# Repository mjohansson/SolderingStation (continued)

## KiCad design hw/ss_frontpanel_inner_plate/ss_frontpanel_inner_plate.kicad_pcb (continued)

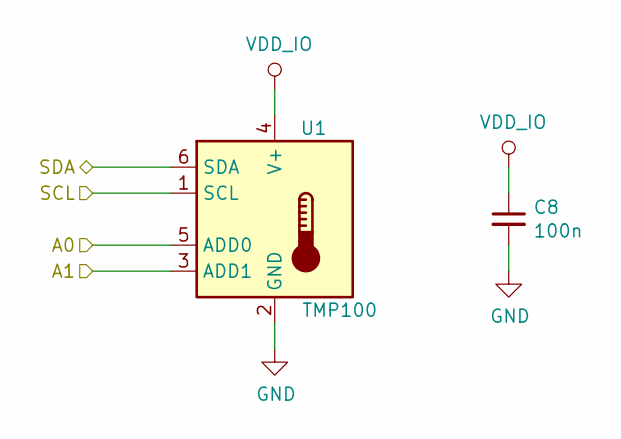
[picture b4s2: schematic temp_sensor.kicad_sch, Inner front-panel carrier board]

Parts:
C8: 100n; C_0603_1608Metric
U1: TMP100; SOT-23-6

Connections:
/SCL: U1.1 (SCL); also elsewhere on the board
/SDA: U1.6 (SDA); also elsewhere on the board
GND: C8.2, U1.2 (GND), U1.3 (ADD1), U1.5 (ADD0); also elsewhere on the board
VDD_IO: C8.1, U1.4 (V+); also elsewhere on the board

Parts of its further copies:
C9, C10, C11, C12: 100n; C_0603_1608Metric
U2, U3, U4, U5: TMP100; SOT-23-6

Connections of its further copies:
/SCL: U2.1 (SCL), U3.1 (SCL), U4.1 (SCL), U5.1 (SCL); also elsewhere on the board
/SDA: U2.6 (SDA), U3.6 (SDA), U4.6 (SDA), U5.6 (SDA); also elsewhere on the board
/TS In mid/A0: U4.5 (ADD0)
GND: C9.2, C10.2, C11.2, C12.2, U2.2 (GND), U2.3 (ADD1), U3.2 (GND), U4.2 (GND), U5.2 (GND), U5.5 (ADD0); also elsewhere on the board
VDD_IO: C9.1, C10.1, C11.1, C12.1, U2.4 (V+), U2.5 (ADD0), U3.3 (ADD1), U3.4 (V+), U3.5 (ADD0), U4.3 (ADD1), U4.4 (V+), U5.3 (ADD1), U5.4 (V+); also elsewhere on the board

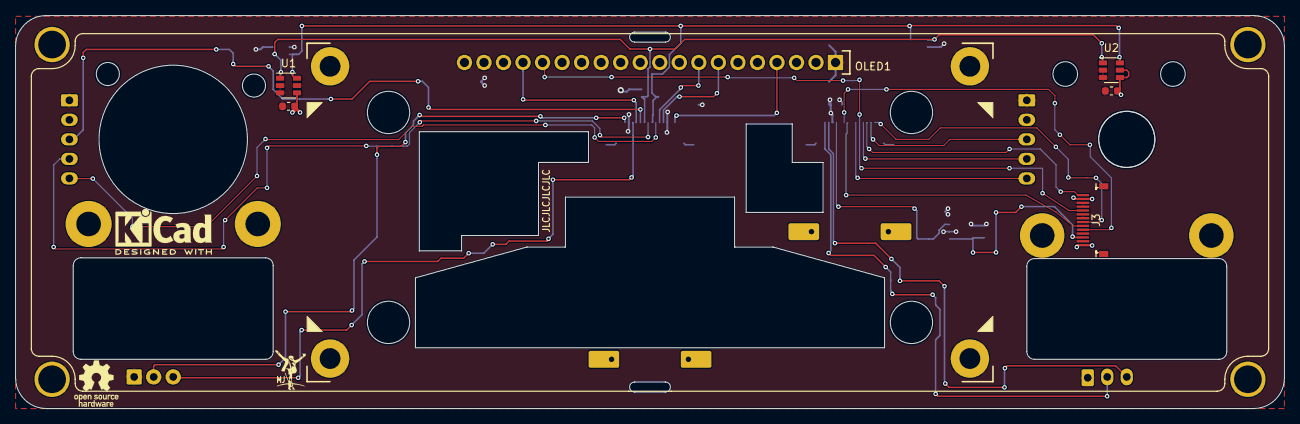
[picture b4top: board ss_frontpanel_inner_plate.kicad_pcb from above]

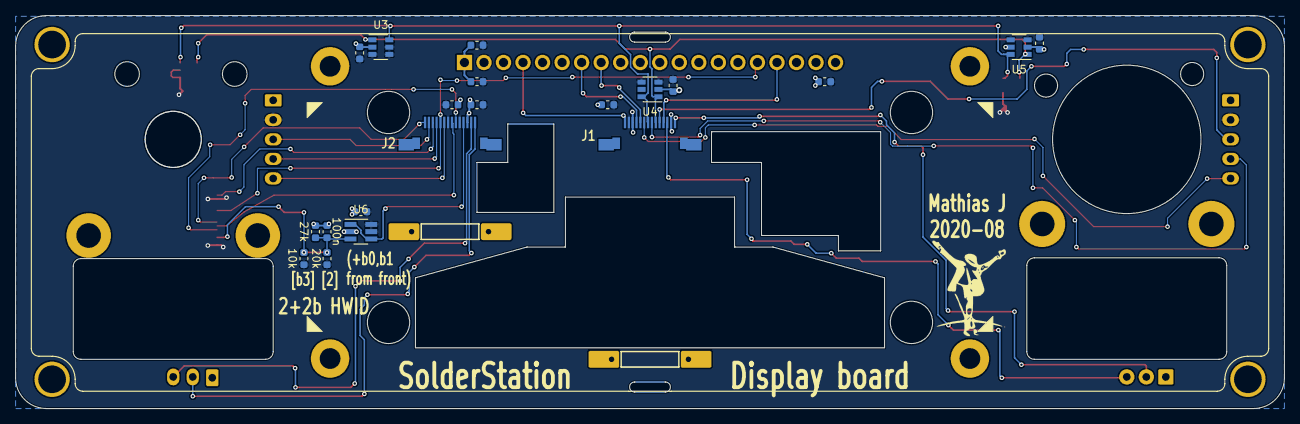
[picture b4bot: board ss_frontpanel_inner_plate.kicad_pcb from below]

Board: 2 copper layers, 165.0 x 51.1 mm, 39 parts (25 on the bottom side), 25 nets.

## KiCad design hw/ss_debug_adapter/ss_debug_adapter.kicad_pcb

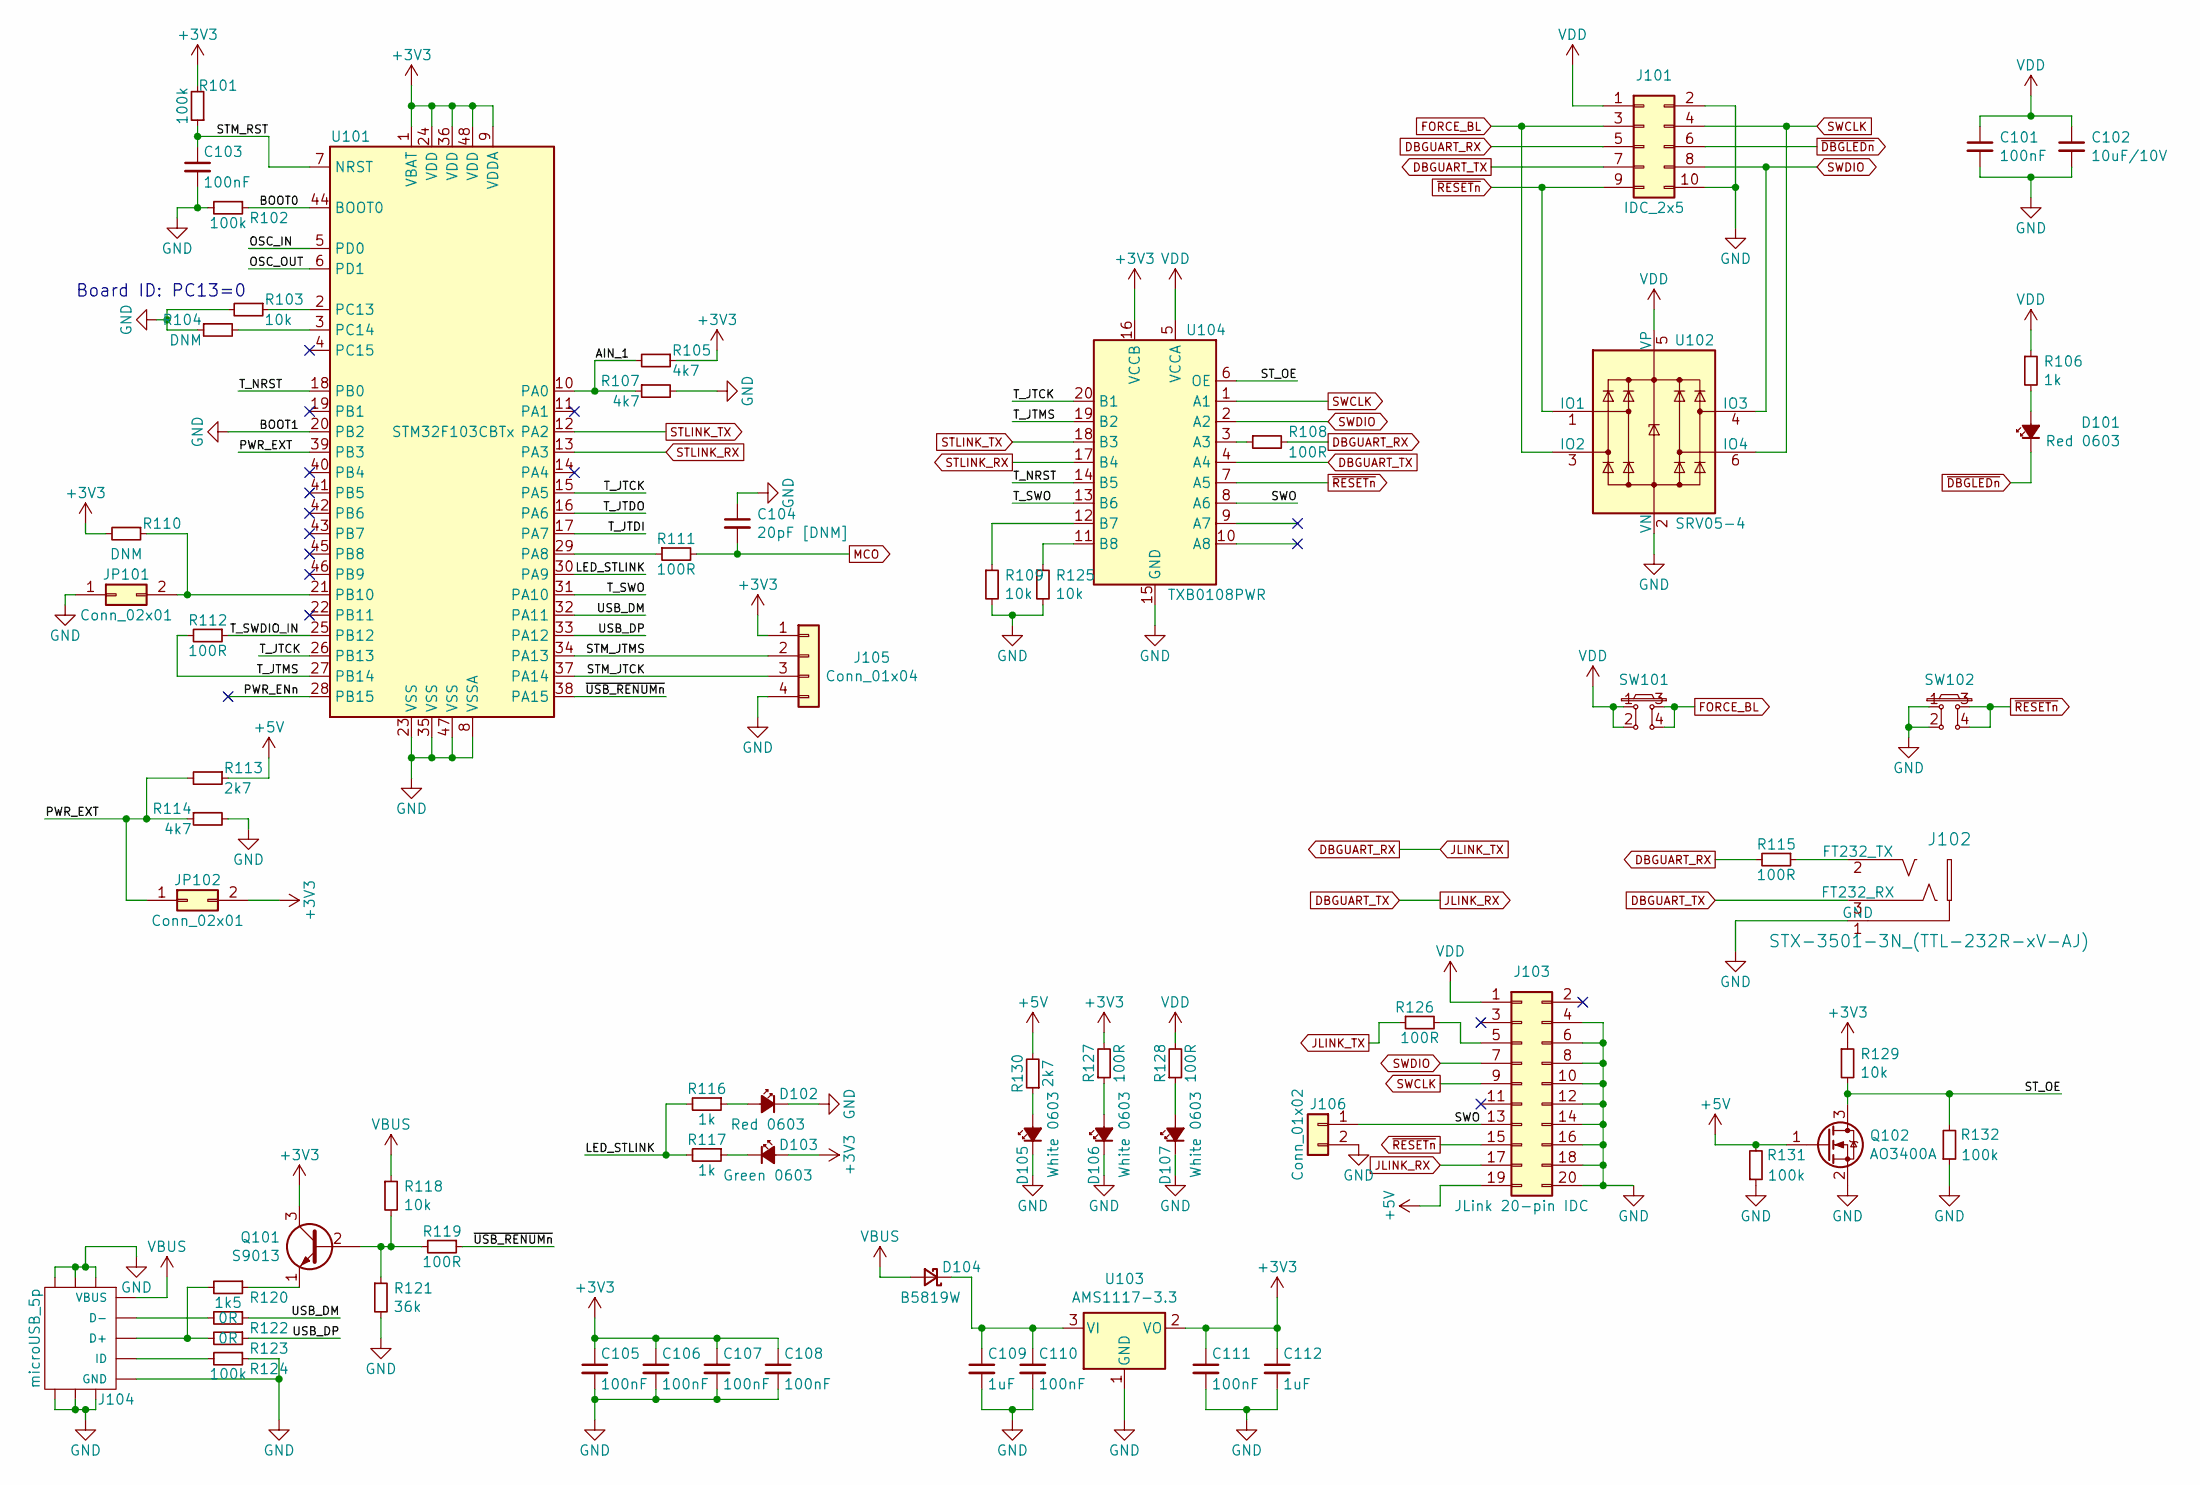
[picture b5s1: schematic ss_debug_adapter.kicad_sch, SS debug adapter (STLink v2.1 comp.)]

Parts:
C101, C103, C105, C106, C107, C108, C110, C111: 100nF; C_0402_1005Metric; LCSC C1525
C102: 10uF/10V; C_0603_1608Metric; LCSC C19702
C104: 20pF [DNM]; C_0402_1005Metric
C109, C112: 1uF; C_0402_1005Metric; LCSC C52923
D101, D102: Red 0603; LED_0603_1608Metric; LCSC C2286
D103: Green 0603; LED_0603_1608Metric; LCSC C72043
D104: B5819W; D_SOD-123; LCSC C6186
D105, D106, D107: White 0603; LED_0603_1608Metric; LCSC C2290
J101: IDC_2x5; IDC-Header_2x05_P2.54mm_Vertical
J102: STX-3501-3N_(TTL-232R-xV-AJ); STX3501_smd
J103: JLink 20-pin IDC; IDC-Header_2x10_P2.54mm_Vertical
J104: microUSB_5p; microUSB_5p-LCSC-Jing_Extension
J105: Conn_01x04; PinHeader_1x04_P2.54mm_Horizontal
J106: Conn_01x02; PinHeader_1x02_P2.54mm_Vertical
JP101, JP102: Conn_02x01; PinHeader_1x02_P2.54mm_Vertical
Q101: S9013; SOT-23; LCSC C6749
Q102: AO3400A; SOT-23
R101, R102, R124, R131, R132: 100k; R_0402_1005Metric; LCSC C25741
R103, R109, R118, R125, R129: 10k; R_0402_1005Metric; LCSC C25744
R104, R110: DNM; R_0402_1005Metric
R105, R107, R114: 4k7; R_0402_1005Metric; LCSC C25900
R106, R116, R117: 1k; R_0402_1005Metric; LCSC C11702
R108, R111, R112, R115, R119, R126, R127, R128: 100R; R_0402_1005Metric; LCSC C25076
R113, R130: 2k7; R_0603_1608Metric; LCSC C13167
R120: 1k5; R_0402_1005Metric; LCSC C25867
R121: 36k; R_0603_1608Metric; LCSC C23147
R122, R123: 0R; R_0402_1005Metric; LCSC C17168
SW101, SW102: Pushbutton_SMD_TS-1102W-4316; SMD_PUSHBTN_6x6mm; LCSC C255812
U101: STM32F103CBTx; LQFP-48_7x7mm_P0.5mm; LCSC C8304
U102: SRV05-4; SOT-23-6; LCSC C85364
U103: AMS1117-3.3; SOT-223-3_TabPin2; LCSC C6186
U104: TXB0108PWR; TSSOP-20_4.4x6.5mm_P0.65mm; JLC Extended

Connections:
+3V3: C105.1, C106.1, C107.1, C108.1, C111.1, C112.1, D103.2 (A), J105.1, JP102.2, Q101.3 (C), R101.2, R105.1, R110.2, R127.2, R129.1, U101.1 (VBAT), U101.9 (VDDA), U101.24 (VDD), U101.36 (VDD), U101.48 (VDD), U103.2 (VO), U104.16 (VCCB)
+5V: J103.19, Q102.1 (G), R113.1, R130.2, R131.2
/AIN_1: R105.2, R107.1, U101.10 (PA0)
/BOOT0: R102.1, U101.44 (BOOT0)
/LED_STLINK: R116.2, R117.2, U101.30 (PA9)
/OSC_IN: U101.5 (PD0)
/OSC_OUT: U101.6 (PD1)
/PWR_ENn: U101.28 (PB15)
/PWR_EXT: JP102.1, R113.2, R114.1, U101.39 (PB3)
/STM_JTCK: J105.3, U101.37 (PA14)
/STM_JTMS: J105.2, U101.34 (PA13)
/STM_RST: C103.1, R101.1, U101.7 (NRST)
/ST_OE: Q102.3 (D), R129.2, R132.2, U104.6 (OE)
/SWO: J103.13, J106.1, U104.8 (A6)
/T_JTCK: U101.15 (PA5), U101.26 (PB13), U104.20 (B1)
/T_JTDI: U101.17 (PA7)
/T_JTDO: U101.16 (PA6)
/T_JTMS: R112.2, U101.27 (PB14), U104.19 (B2)
/T_NRST: U101.18 (PB0), U104.14 (B5)
/T_SWDIO_IN: R112.1, U101.25 (PB12)
/T_SWO: U101.31 (PA10), U104.13 (B6)
/USB_DM: R122.1, U101.32 (PA11)
/USB_DP: R123.1, U101.33 (PA12)
/~USB_RENUMn: R119.1, U101.38 (PA15)
DBGUART_RX: J101.5, R108.2, R115.2, R126.1
DBGUART_TX: J101.7, J102.3 (FT232_RX), J103.17, U104.4 (A4)
FORCE_BL: J101.3, SW101.3, SW101.4, U102.3 (IO2)
GND: C101.2, C102.2, C103.2, C104.1, C105.2, C106.2, C107.2, C108.2, C109.2, C110.2, C111.2, C112.2, D102.1 (K), D105.1 (K), D106.1 (K), D107.1 (K), J101.2, J101.10, J102.1 (GND), J103.4, J103.6, J103.8, J103.10, J103.12, J103.14, J103.16, J103.18, J103.20, J104.5 (GND), J104.6, J104.7, J104.8, J104.9, J104.10, J104.11, J105.4, J106.2, JP101.1, Q102.2 (S), R102.2, R103.2, R104.1, R107.2, R109.2, R114.2, R121.2, R124.1, R125.2, R131.1, R132.1, SW102.1, SW102.2, U101.8 (VSSA), U101.20 (PB2), U101.23 (VSS), U101.35 (VSS), U101.47 (VSS), U102.2 (VN), U103.1 (GND), U104.15 (GND)
MCO: C104.2, R111.2
unnamed: C109.1, C110.1, D104.1 (K), U103.3 (VI)
unnamed: D101.2 (A), R106.2
unnamed: D102.2 (A), R116.1
unnamed: D103.1 (K), R117.1
unnamed: D105.2 (A), R130.1
unnamed: D106.2 (A), R127.1
unnamed: D107.2 (A), R128.1
unnamed: J102.2 (FT232_TX), R115.1
unnamed: J103.5, R126.2
unnamed: J104.2 (D-), R122.2
unnamed: J104.3 (D+), R120.2, R123.2
unnamed: J104.4 (ID), R124.2
unnamed: JP101.2, R110.1, U101.21 (PB10)
unnamed: Q101.1 (E), R120.1
unnamed: Q101.2 (B), R118.2, R119.2, R121.1
unnamed: R103.1, U101.2 (PC13)
unnamed: R104.2, U101.3 (PC14)
unnamed: R108.1, U104.3 (A3)
unnamed: R109.1, U104.12 (B7)
unnamed: R111.1, U101.29 (PA8)
unnamed: R125.1, U104.11 (B8)
STLINK_RX: U101.13 (PA3), U104.17 (B4)
STLINK_TX: U101.12 (PA2), U104.18 (B3)
SWCLK: J101.4, J103.9, U102.6 (IO4), U104.1 (A1)
SWDIO: J101.8, J103.7, U102.4 (IO3), U104.2 (A2)
VBUS: D104.2 (A), J104.1 (VBUS), R118.1
VDD: C101.1, C102.1, J101.1, J103.1, R106.1, R128.2, SW101.1, SW101.2, U102.5 (VP), U104.5 (VCCA)
~DBGLEDn: D101.1 (K), J101.6
~RESETn: J101.9, J103.15, SW102.3, SW102.4, U102.1 (IO1), U104.7 (A5)

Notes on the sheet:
Board ID: PC13=0

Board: 2 copper layers, 67 parts (1 on the bottom side), 53 nets, no tracks yet.

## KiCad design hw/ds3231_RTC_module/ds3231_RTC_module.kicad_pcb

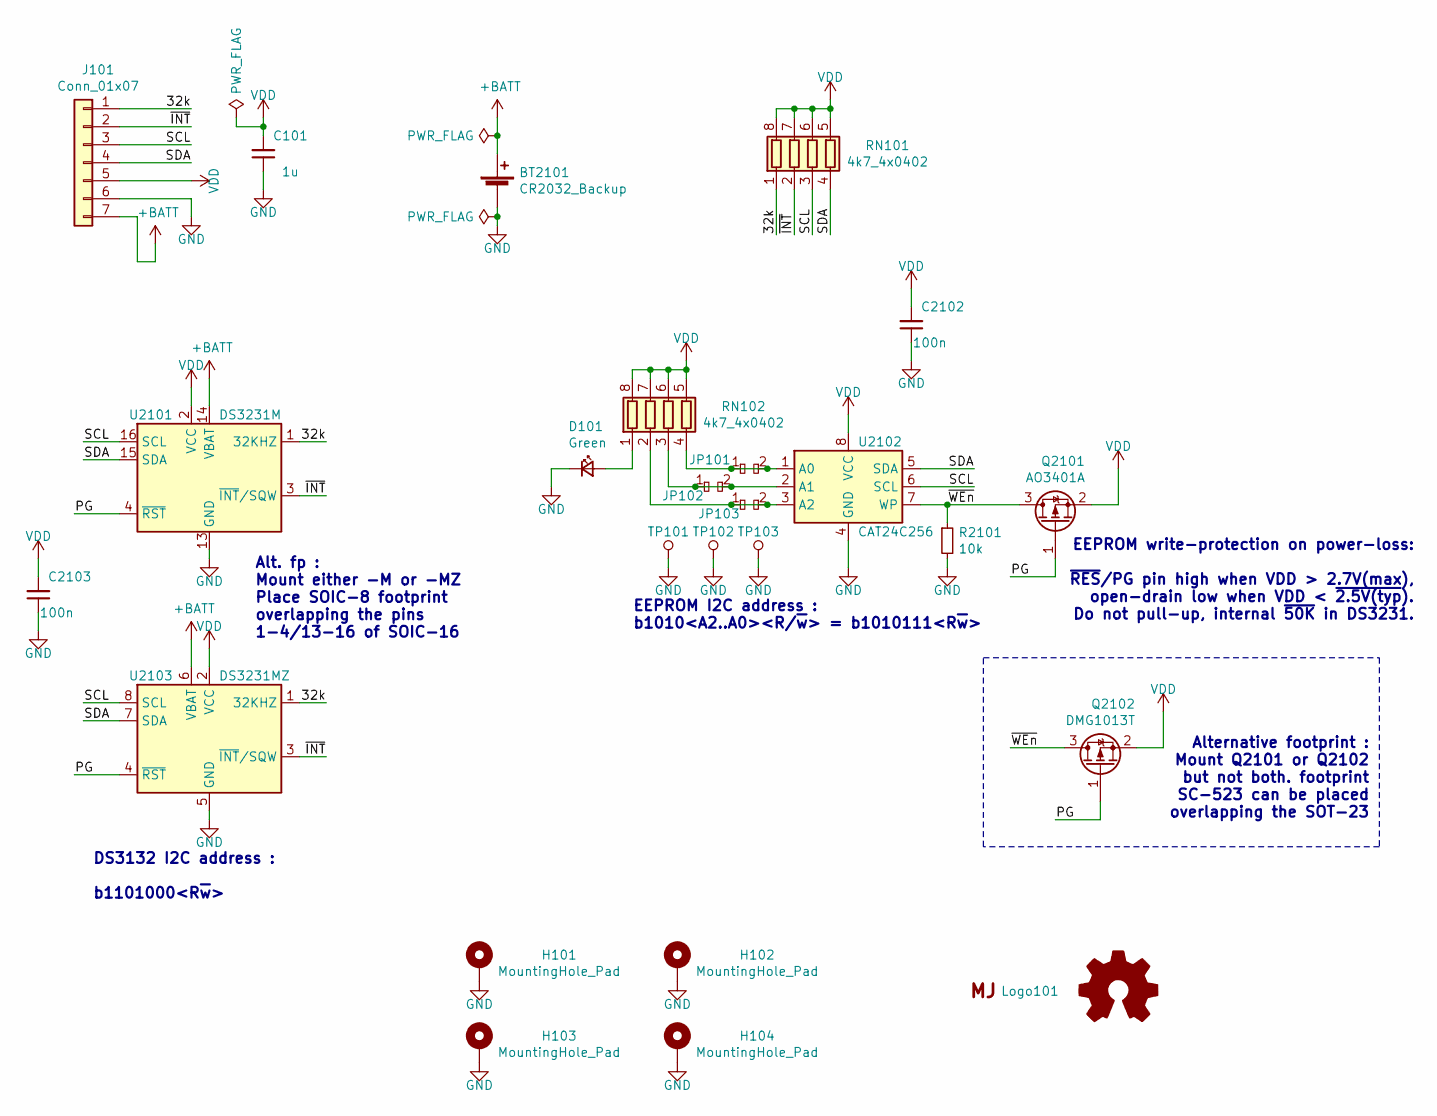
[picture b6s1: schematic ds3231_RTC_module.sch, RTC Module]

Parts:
BT2101: CR2032_Backup; CR2032_coincell_holder
C101: 1u; C_0603_1608Metric
C2102, C2103: 100n; C_0402_1005Metric
D101: Green; LED_0402_1005Metric
H101, H102, H103, H104: MountingHole_Pad; MountingHole_3.2mm_M3_DIN965_Pad
J101: Conn_01x07; PinHeader_1x07_P2.54mm_Vertical
JP101, JP102, JP103: dogbone_2_ud; db2_ud_0402
LOGO101: Logo_Open_Hardware_Small; OSHW-Logo2_7.3x6mm_SilkScreen
Logo101: Logo_MJ; MJ_Mini
Q2101: AO3401A; SOT-23
Q2102: DMG1013T; SOT-523
R2101: 10k; R_0402_1005Metric
RN101, RN102: 4k7_4x0402; R_Array_Convex_4x0402
TP101, TP102, TP103: TP; TP_SMD_1.2c
U2101: DS3231M; SOIC-16W_7.5x10.3mm_P1.27mm
U2102: CAT24C256; SO-8_3.9x4.9mm_P1.27mm
U2103: DS3231MZ; SOIC-8_3.9x4.9mm_P1.27mm

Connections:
+BATT: BT2101.1 (+), J101.7, U2101.14 (VBAT), U2103.6 (VBAT)
/32k: J101.1, RN101.1 (R1.1), U2101.1 (32KHZ), U2103.1 (32KHZ)
/PG: Q2101.1 (G), Q2102.1 (G), U2101.4 (~RST), U2103.4 (~RST)
/SCL: J101.3, RN101.3 (R3.1), U2101.16 (SCL), U2102.6 (SCL), U2103.8 (SCL)
/SDA: J101.4, RN101.4 (R4.1), U2101.15 (SDA), U2102.5 (SDA), U2103.7 (SDA)
/~INT~: J101.2, RN101.2 (R2.1), U2101.3 (~INT~/SQW), U2103.3 (~INT~/SQW)
/~WEn~: Q2101.3 (D), Q2102.3 (D), R2101.1, U2102.7 (WP)
GND: BT2101.2 (-), C101.1, C2102.1, C2103.1, D101.1 (K), H101.1, H102.1, H103.1, H104.1, J101.6, R2101.2, TP101.1, TP102.1, TP103.1, U2101.5 (GND), U2101.6 (GND), U2101.7 (GND), U2101.8 (GND), U2101.9 (GND), U2101.10 (GND), U2101.11 (GND), U2101.12 (GND), U2101.13 (GND), U2102.4 (GND), U2103.5 (GND)
unnamed: D101.2 (A), RN102.1 (R1.1)
unnamed: JP101.1, JP101.2, RN102.4 (R4.1), U2102.1 (A0)
unnamed: JP102.1, JP102.2, RN102.3 (R3.1), U2102.2 (A1)
unnamed: JP103.1, JP103.2, RN102.2 (R2.1), U2102.3 (A2)
VDD: C101.2, C2102.2, C2103.2, J101.5, Q2101.2 (S), Q2102.2 (S), RN101.5 (R4.2), RN101.6 (R3.2), RN101.7 (R2.2), RN101.8 (R1.2), RN102.5 (R4.2), RN102.6 (R3.2), RN102.7 (R2.2), RN102.8 (R1.2), U2101.2 (VCC), U2102.8 (VCC), U2103.2 (VCC)

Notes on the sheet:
Alt. fp : Mount either -M or -MZ Place SOIC-8 footprint overlapping the pins 1-4/13-16 of SOIC-16
EEPROM write-protection on power-loss: ~RES~/PG pin high when VDD > 2.7V(max), open-drain low when VDD < ~2.5V(typ). Do not pull-up, internal ~50K in DS3231.
EEPROM I2C address : b1010<A2..A0><R/~w~> = b1010111<R~w~>
DS3132 I2C address : b1101000<R~w~>
Alternative footprint : Mount Q2101 or Q2102 but not both. footprint SC-523 can be placed overlapping the SOT-23

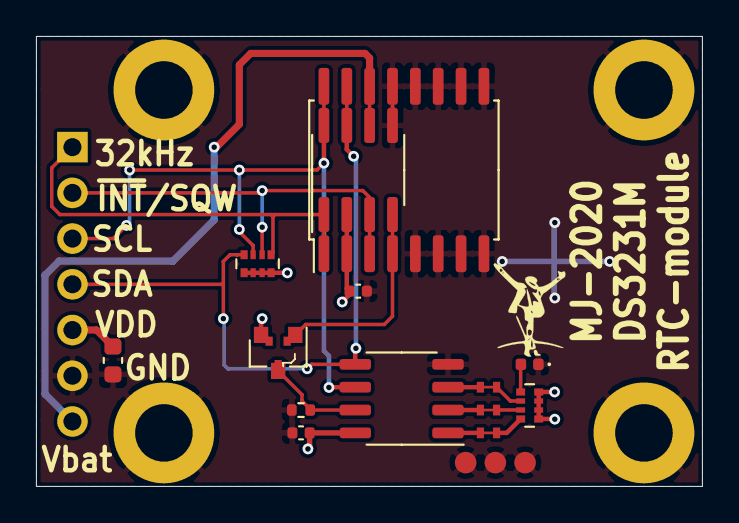
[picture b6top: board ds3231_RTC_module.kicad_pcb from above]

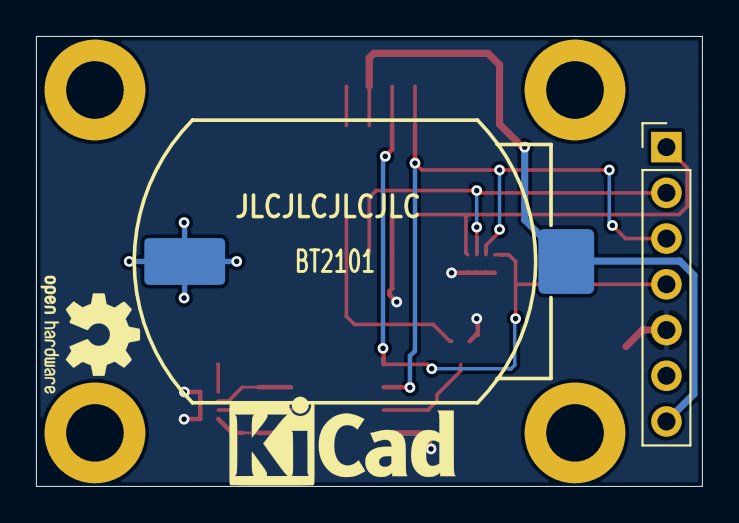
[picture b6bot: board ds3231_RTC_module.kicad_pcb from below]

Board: 2 copper layers, 37.0 x 25.0 mm, 26 parts (3 on the bottom side), 13 nets.

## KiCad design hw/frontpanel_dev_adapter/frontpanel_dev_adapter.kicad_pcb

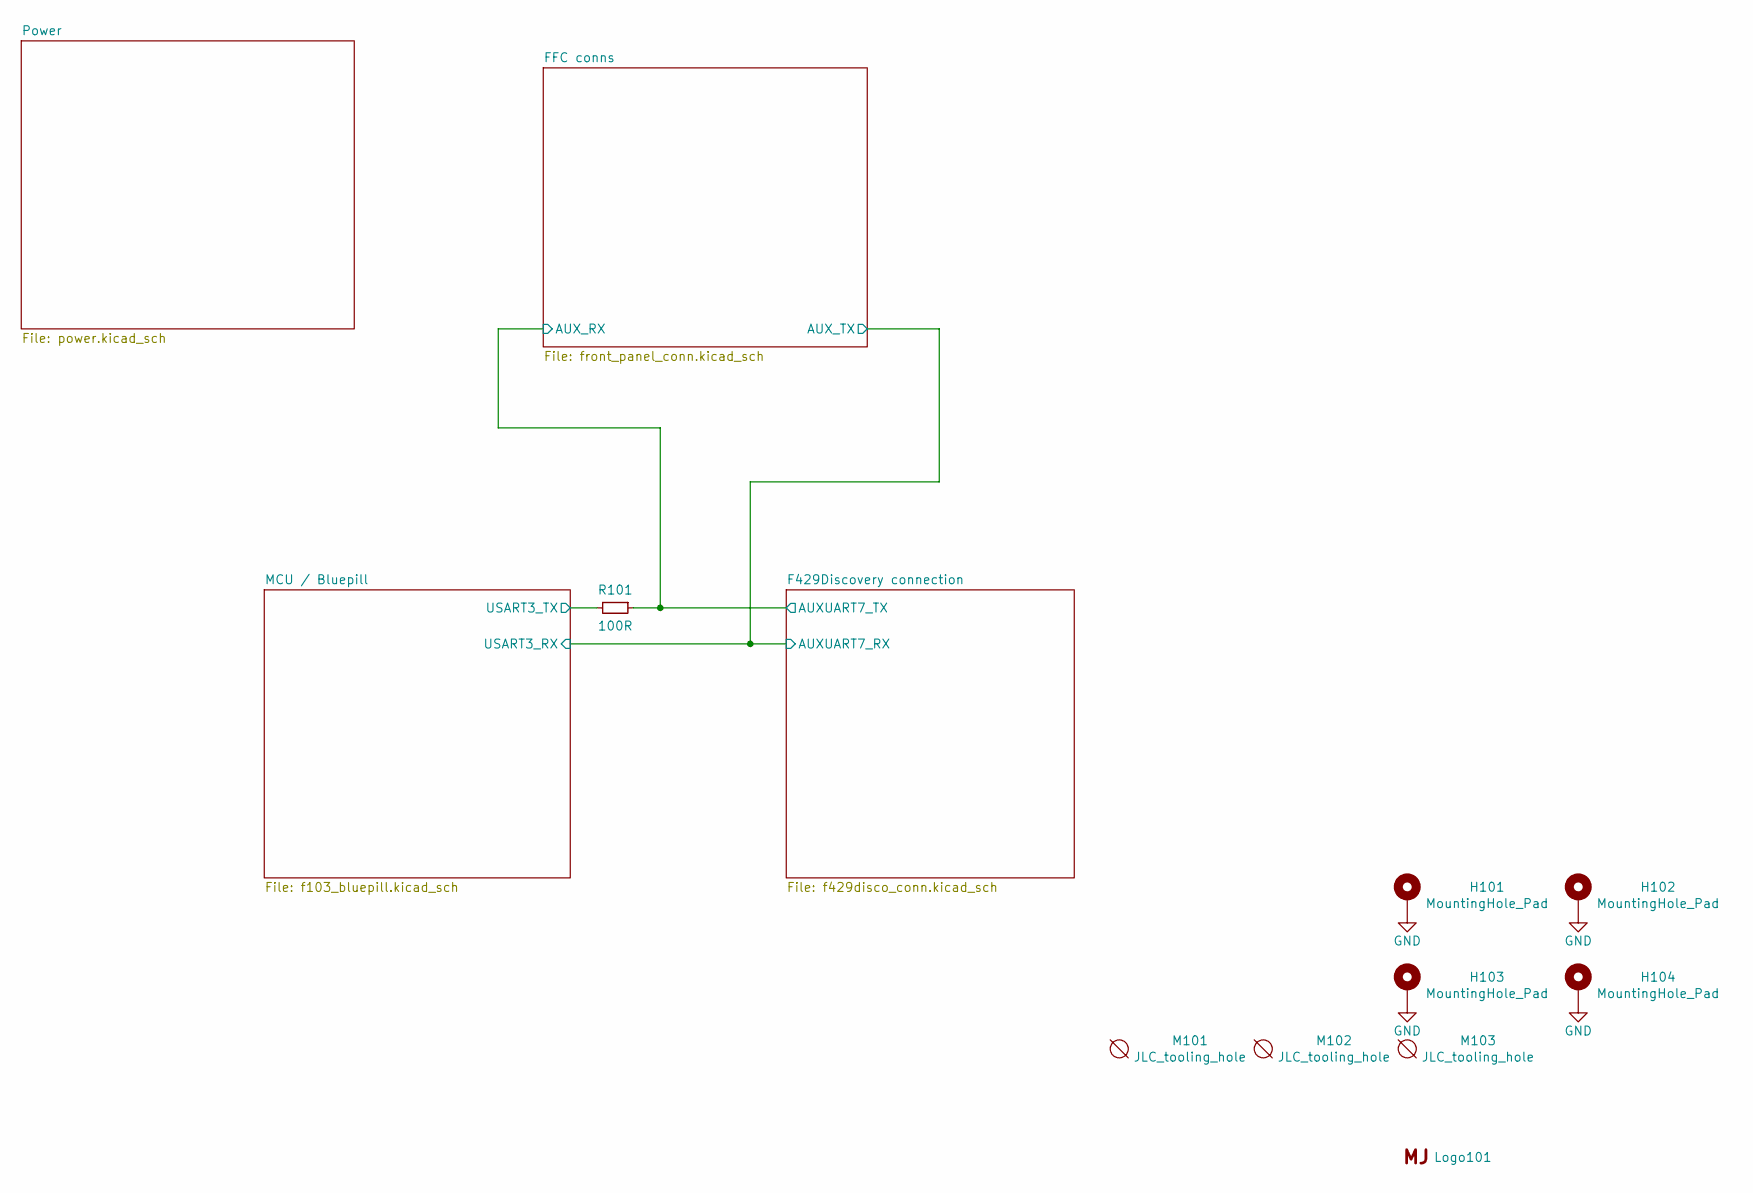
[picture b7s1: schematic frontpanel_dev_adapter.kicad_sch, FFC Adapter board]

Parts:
H101, H102, H103, H104: MountingHole_Pad; MountingHole_3.2mm_M3_ISO7380_Pad
Logo101: Logo_MJ; MJ_10.3x12.7
M101, M102, M103: JLC_tooling_hole; JLC_tooling-hole
R101: 100R; R_0402_1005Metric; LCSC C25076

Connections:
/F429Discovery connection/AUXUART7_TX: R101.1; also elsewhere on the board
/MCU / Bluepill/USART3_TX: R101.2; also elsewhere on the board

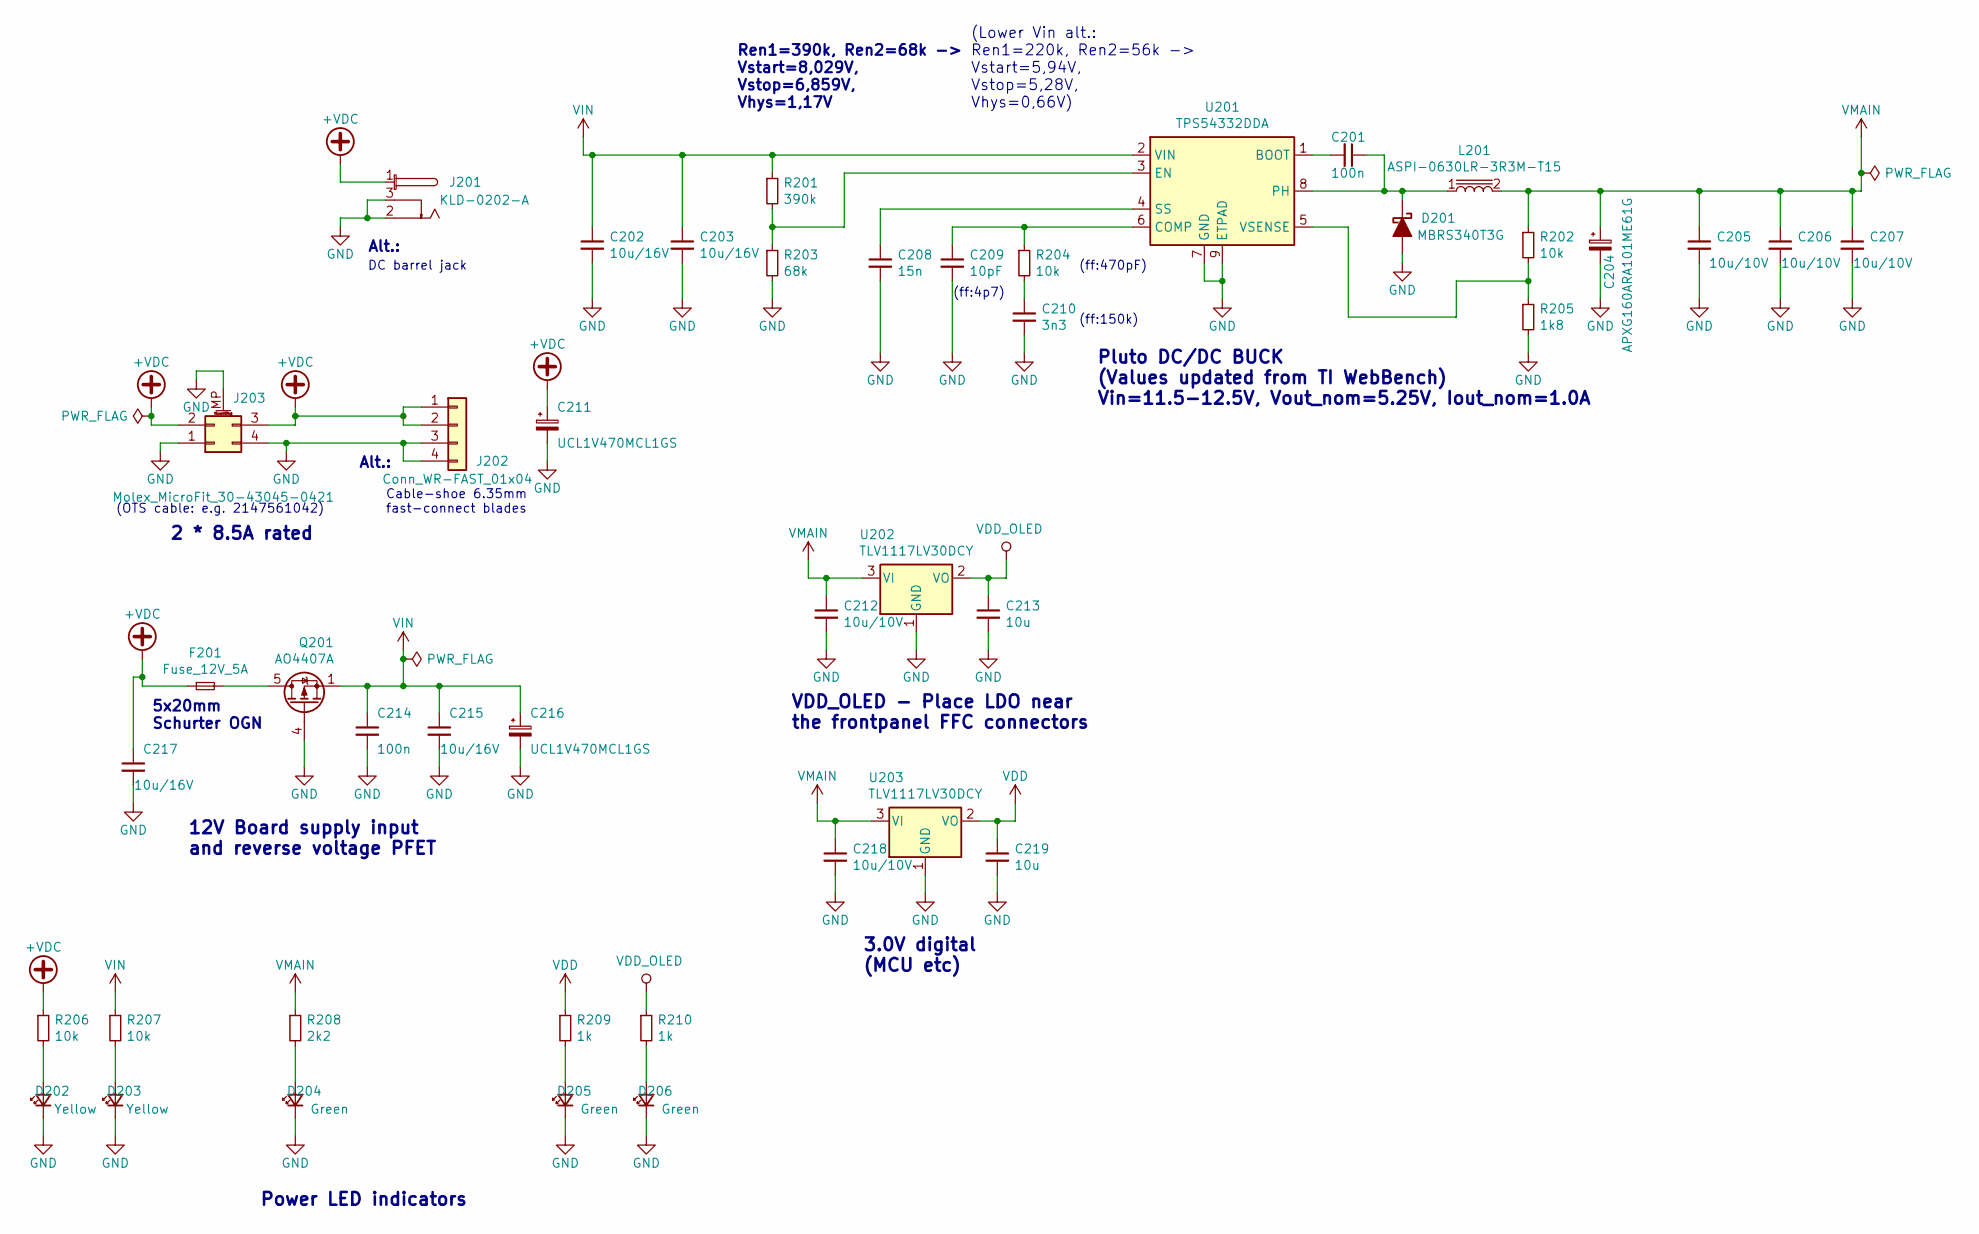
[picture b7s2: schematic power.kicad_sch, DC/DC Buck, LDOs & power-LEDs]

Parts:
C201, C214: 100n; C_0603_1608Metric; LCSC C14663
C202, C203, C215, C217: 10u/16V; C_0805_2012Metric; LCSC C15850
C204: APXG160ARA101ME61G; CP_Elec_5x5.8
C205, C206, C207, C212, C218: 10u/10V; C_0603_1608Metric; LCSC C19702
C208: 15n; C_0603_1608Metric; LCSC C1596
C209: 10pF; C_0402_1005Metric; LCSC C32949
C210: 3n3; C_0402_1005Metric; LCSC C26404
C211, C216: UCL1V470MCL1GS; CP_Elec_6.3x5.8
C213, C219: 10u; C_0603_1608Metric; LCSC C19702
D201: MBRS340T3G; MBRS3xx_SMC_CASE_403AC; LCSC C40326
D202, D203: Yellow; LED_0603_1608Metric; LCSC C72038
D204, D205, D206: Green; LED_0603_1608Metric; LCSC C72043
F201: Fuse_12V_5A; Fuseholder_5x20mm_Schurter_OGN-0031.8201
J201: KLD-0202-A
J202: Conn_WR-FAST_01x04; WR-FAST_508_4_V
J203: Molex_MicroFit_30-43045-0421; Molex_Micro-Fit_3.0_43045-0421_2x02-1MP_P3.00mm_Horizontal
L201: ASPI-0630LR-3R3M-T15; ASPI-0603LR
Q201: AO4407A; SOIC-8_3.9x4.9mm_P1.27mm; LCSC C16072
R201: 390k; R_0603_1608Metric; LCSC C23150
R202, R204, R206, R207: 10k; R_0402_1005Metric; LCSC C25744
R203: 68k; R_0402_1005Metric; LCSC C36871
R205: 1k8; R_0603_1608Metric; LCSC C4177
R208: 2k2; R_0402_1005Metric; LCSC C25879
R209, R210: 1k; R_0402_1005Metric; LCSC C11702
U201: TPS54332DDA; TI_SO-PowerPAD-8_ThermalVias; LCSC C41312
U202, U203: TLV1117LV30DCY; SOT-223-3_TabPin2; LCSC C15578

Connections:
+VDC: C211.1, C217.1, F201.1, J201.1, J202.1, J202.2, J203.2, J203.3, R206.1
unnamed: C201.2, U201.1 (BOOT)
unnamed: C209.1, R204.1, U201.6 (COMP)
unnamed: C210.1, R204.2
unnamed: D202.2 (A), R206.2
unnamed: D203.2 (A), R207.2
unnamed: D204.2 (A), R208.2
unnamed: D205.2 (A), R209.2
unnamed: D206.2 (A), R210.2
unnamed: F201.2, Q201.5 (D), Q201.6 (D), Q201.7 (D), Q201.8 (D)
unnamed: R202.2, R205.1, U201.5 (VSENSE)
VDD: C219.1, R209.1, U203.2 (VO); also elsewhere on the board
VDD_OLED: C213.1, R210.1, U202.2 (VO); also elsewhere on the board
VIN: C202.1, C203.1, C214.1, C215.1, C216.1, Q201.1 (S), Q201.2 (S), Q201.3 (S), R201.1, R207.1, U201.2 (VIN); also elsewhere on the board
VMAIN: C204.1, C205.1, C206.1, C207.1, C212.1, C218.1, L201.2, R202.1, R208.1, U202.3 (VI), U203.3 (VI); also elsewhere on the board

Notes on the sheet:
Ren1=390k, Ren2=68k -> Vstart=8,029V, Vstop=6,859V, Vhys=1,17V
(Lower Vin alt.: Ren1=220k, Ren2=56k -> Vstart=5,94V, Vstop=5,28V, Vhys=0,66V)
Alt.:
(ff:470pF)
Cable-shoe 6.35mm fast-connect blades
(ff:150k)
2 * 8.5A rated
Power LED indicators
(OTS cable: e.g. 2147561042)
5x20mm Schurter OGN
Pluto DC/DC BUCK (Values updated from TI WebBench) Vin=11.5-12.5V, Vout_nom=5.25V, Iout_nom=1.0A
VDD_OLED - Place LDO near the frontpanel FFC connectors
(ff:4p7)
DC barrel jack
12V Board supply input and reverse voltage PFET
3.0V digital (MCU etc)

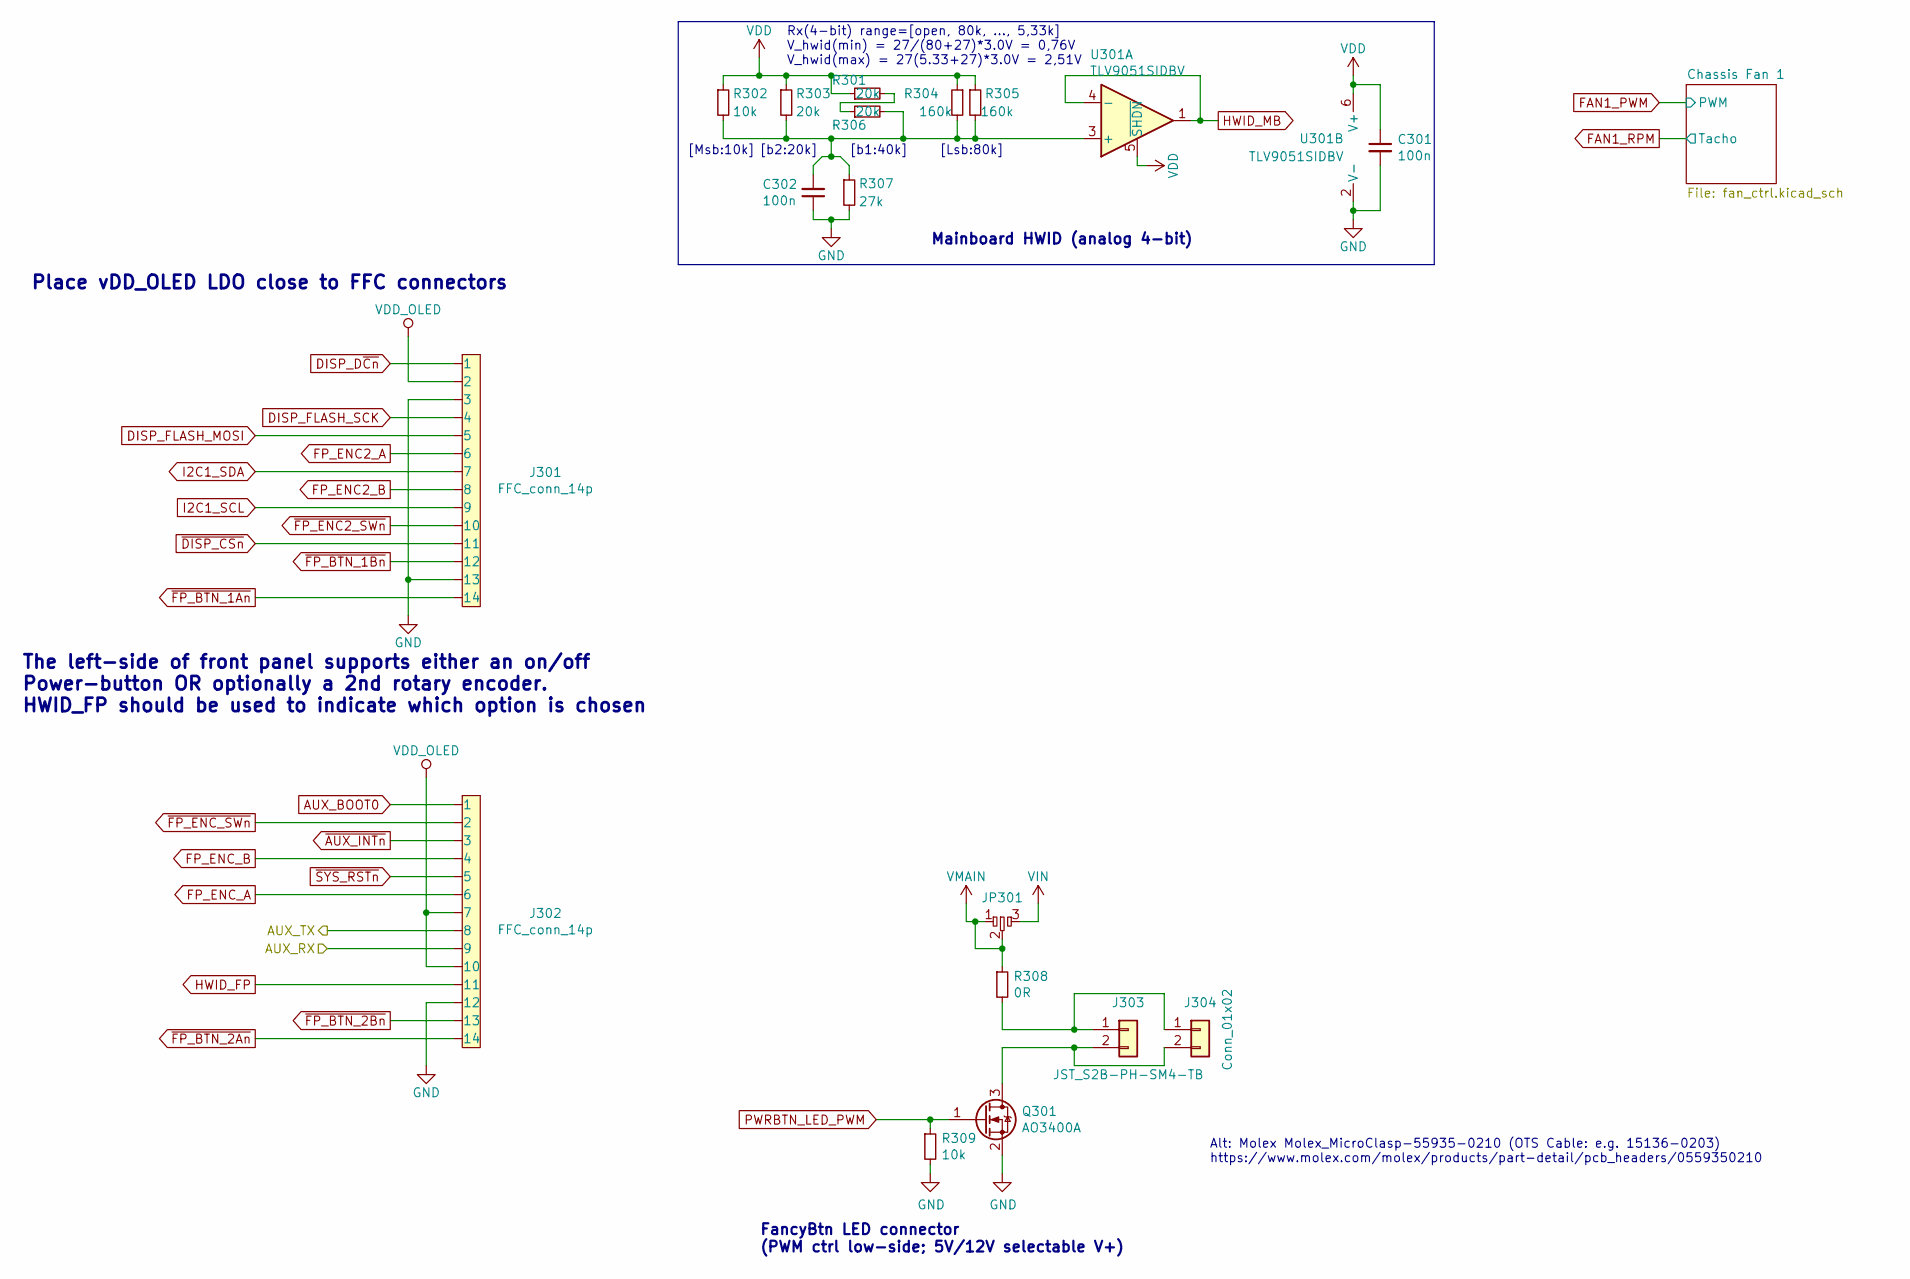
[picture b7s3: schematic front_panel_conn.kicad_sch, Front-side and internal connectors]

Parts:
C301, C302: 100n; C_0402_1005Metric; LCSC C1525
J301, J302: FFC_conn_14p; FPC_14p_05mm-Molex_5052781433
J303: JST_S2B-PH-SM4-TB; JST_PH_S2B-PH-SM4-TB_1x02-1MP_P2.00mm_Horizontal
J304: Conn_01x02; PinHeader_1x02_P2.54mm_Vertical
JP301: dogbone_3_ud; db3_ud_0603
Q301: AO3400A; SOT-23; LCSC C20917
R301, R303, R306: 20k; R_0402_1005Metric; LCSC C25765
R302, R309: 10k; R_0402_1005Metric; LCSC C25744
R304, R305: 160k; R_0603_1608Metric; LCSC C22813
R307: 27k; R_0402_1005Metric; LCSC C25771
R308: 0R; R_0402_1005Metric; LCSC C17168
U301: TLV9051SIDBV; TSOT-23-6

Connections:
/F429Discovery connection/AUXUART7_RX: J302.8; also elsewhere on the board
/F429Discovery connection/AUXUART7_TX: J302.9; also elsewhere on the board
AUX_BOOT0: J302.1; also elsewhere on the board
DISP_D~Cn~: J301.1; also elsewhere on the board
DISP_FLASH_MOSI: J301.5; also elsewhere on the board
DISP_FLASH_SCK: J301.4; also elsewhere on the board
FP_ENC2_A: J301.6; also elsewhere on the board
FP_ENC2_B: J301.8; also elsewhere on the board
FP_ENC_A: J302.6; also elsewhere on the board
FP_ENC_B: J302.4; also elsewhere on the board
HWID_FP: J302.11; also elsewhere on the board
HWID_MB: U301.1, U301.4 (-); also elsewhere on the board
I2C1_SCL: J301.9; also elsewhere on the board
I2C1_SDA: J301.7; also elsewhere on the board
unnamed: C302.2, R302.2, R303.2, R304.2, R305.2, R306.2, R307.1, U301.3 (+)
unnamed: J303.1, J304.1, R308.2
unnamed: J303.2, J304.2, Q301.3 (D)
unnamed: R301.2, R306.1
PWRBTN_LED_PWM: Q301.1 (G), R309.1; also elsewhere on the board
VDD: C301.1, R301.1, R302.1, R303.1, R304.1, R305.1, U301.5 (~SHDN), U301.6 (V+); also elsewhere on the board
VDD_OLED: J301.2, J302.7, J302.10; also elsewhere on the board
VIN: JP301.3; also elsewhere on the board
VMAIN: JP301.1, JP301.2, R308.1; also elsewhere on the board
~AUX_INTn~: J302.3; also elsewhere on the board
~DISP_CSn~: J301.11; also elsewhere on the board
~FP_BTN_1An~: J301.14; also elsewhere on the board
~FP_BTN_1Bn~: J301.12; also elsewhere on the board
~FP_BTN_2An~: J302.14; also elsewhere on the board
~FP_BTN_2Bn~: J302.13; also elsewhere on the board
~FP_ENC2_SWn~: J301.10; also elsewhere on the board
~FP_ENC_SWn~: J302.2; also elsewhere on the board
~SYS_RSTn~: J302.5; also elsewhere on the board

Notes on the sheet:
The left-side of front panel supports either an on/off Power-button OR optionally a 2nd rotary encoder. HWID_FP should be used to indicate which option is chosen
[Msb:10k]
[b1:40k]
Mainboard HWID (analog 4-bit)
[b2:20k]
Alt: Molex Molex_MicroClasp-55935-0210 (OTS Cable: e.g. 15136-0203) https://www.molex.com/molex/products/part-detail/pcb_headers/0559350210
FancyBtn LED connector (PWM ctrl low-side; 5V/12V selectable V+)
Rx(4-bit) range=[open, 80k, ..., 5,33k] V_hwid(min) = 27/(80+27)*3.0V = 0,76V V_hwid(max) = 27(5.33+27)*3.0V = 2,51V
[Lsb:80k]
Place vDD_OLED LDO close to FFC connectors
